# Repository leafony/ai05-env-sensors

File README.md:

# AI05 Env Sensors

温湿度・気圧・3軸加速度を測定する Leafony リーフの KiCad プロジェクトです。

## 構成部品

| 部品 | メーカー | 機能 |
| --- | --- | --- |
| SHT40-AD1B-R2 | Sensirion | 温湿度（選択実装） |
| SGP40-D-R4 | Sensirion | VOC ガス（選択実装） |
| BME280 / BME680 | Bosch Sensortec | 温湿度・気圧 / 温湿度・気圧・ガス（選択実装） |
| LIS2DW12TR | STMicroelectronics | 3軸加速度 |
| SM04B-SRSS-TB | JST | Qwiic、4極、1 mm ピッチ、横出し |

全センサーは Leafony Bus の **3.3 V・I²C** に接続します。基板は **23 × 20 mm、4層、板厚 0.8 mm** です。

SHT40とSGP40は現行の回路図・BOMではDNPです。標準構成ではBME280とLIS2DW12を実装します。

BME280 と BME680 は専用フットプリントをそれぞれ設け、**片方だけを実装**します。標準構成は BME280（U3、C5、C6）を実装し、BME680（U4、C7、C8）を DNP とします。BME680 構成ではこの実装・未実装を入れ替えます。

| センサー | I²C アドレス |
| --- | --- |
| SHT40 | `0x44` |
| SGP40 | `0x59` |
| BME280 / BME680 | `0x76` |
| LIS2DW12 | `0x18`（SDO/SA0をGNDに接続） |

LIS2DW12 の割り込み端子はD3に接続されます。I2C通信速度の上限は 400 kHz です。

SDA/SCL のプルアップはAP03 STM32リーフに搭載されているためDNPとします。既存 AI01 4-Sensors とは加速度センサーの割り込みピンD3が重複するため、同じバスに同時接続しないでください。

## サンプルコード

[`platformio/`](platformio/README.md) にサンプルをフォルダごとの独立したPlatformIOプロジェクトとして配置しています。[`read_sensors`](platformio/read_sensors/README.md) はAP03 STM32向けに、起動時にセンサーを検出・初期化し、1秒ごとに測定値をシリアル（115200 bps）へ出力します。未実装センサーはスキップします。

[`accel_wakeup`](platformio/accel_wakeup/README.md) はLIS2DW12の動き検出をD3の割り込みで受け取り、検出時刻・回数・軸・加速度をシリアル出力します。

[`accel_shock_fifo`](platformio/accel_shock_fifo/README.md) は衝撃検出後の加速度100点をFIFOから取得します。付属のブラウザービューアで3軸の波形表示とCSV保存ができます。

## ライセンス

MIT

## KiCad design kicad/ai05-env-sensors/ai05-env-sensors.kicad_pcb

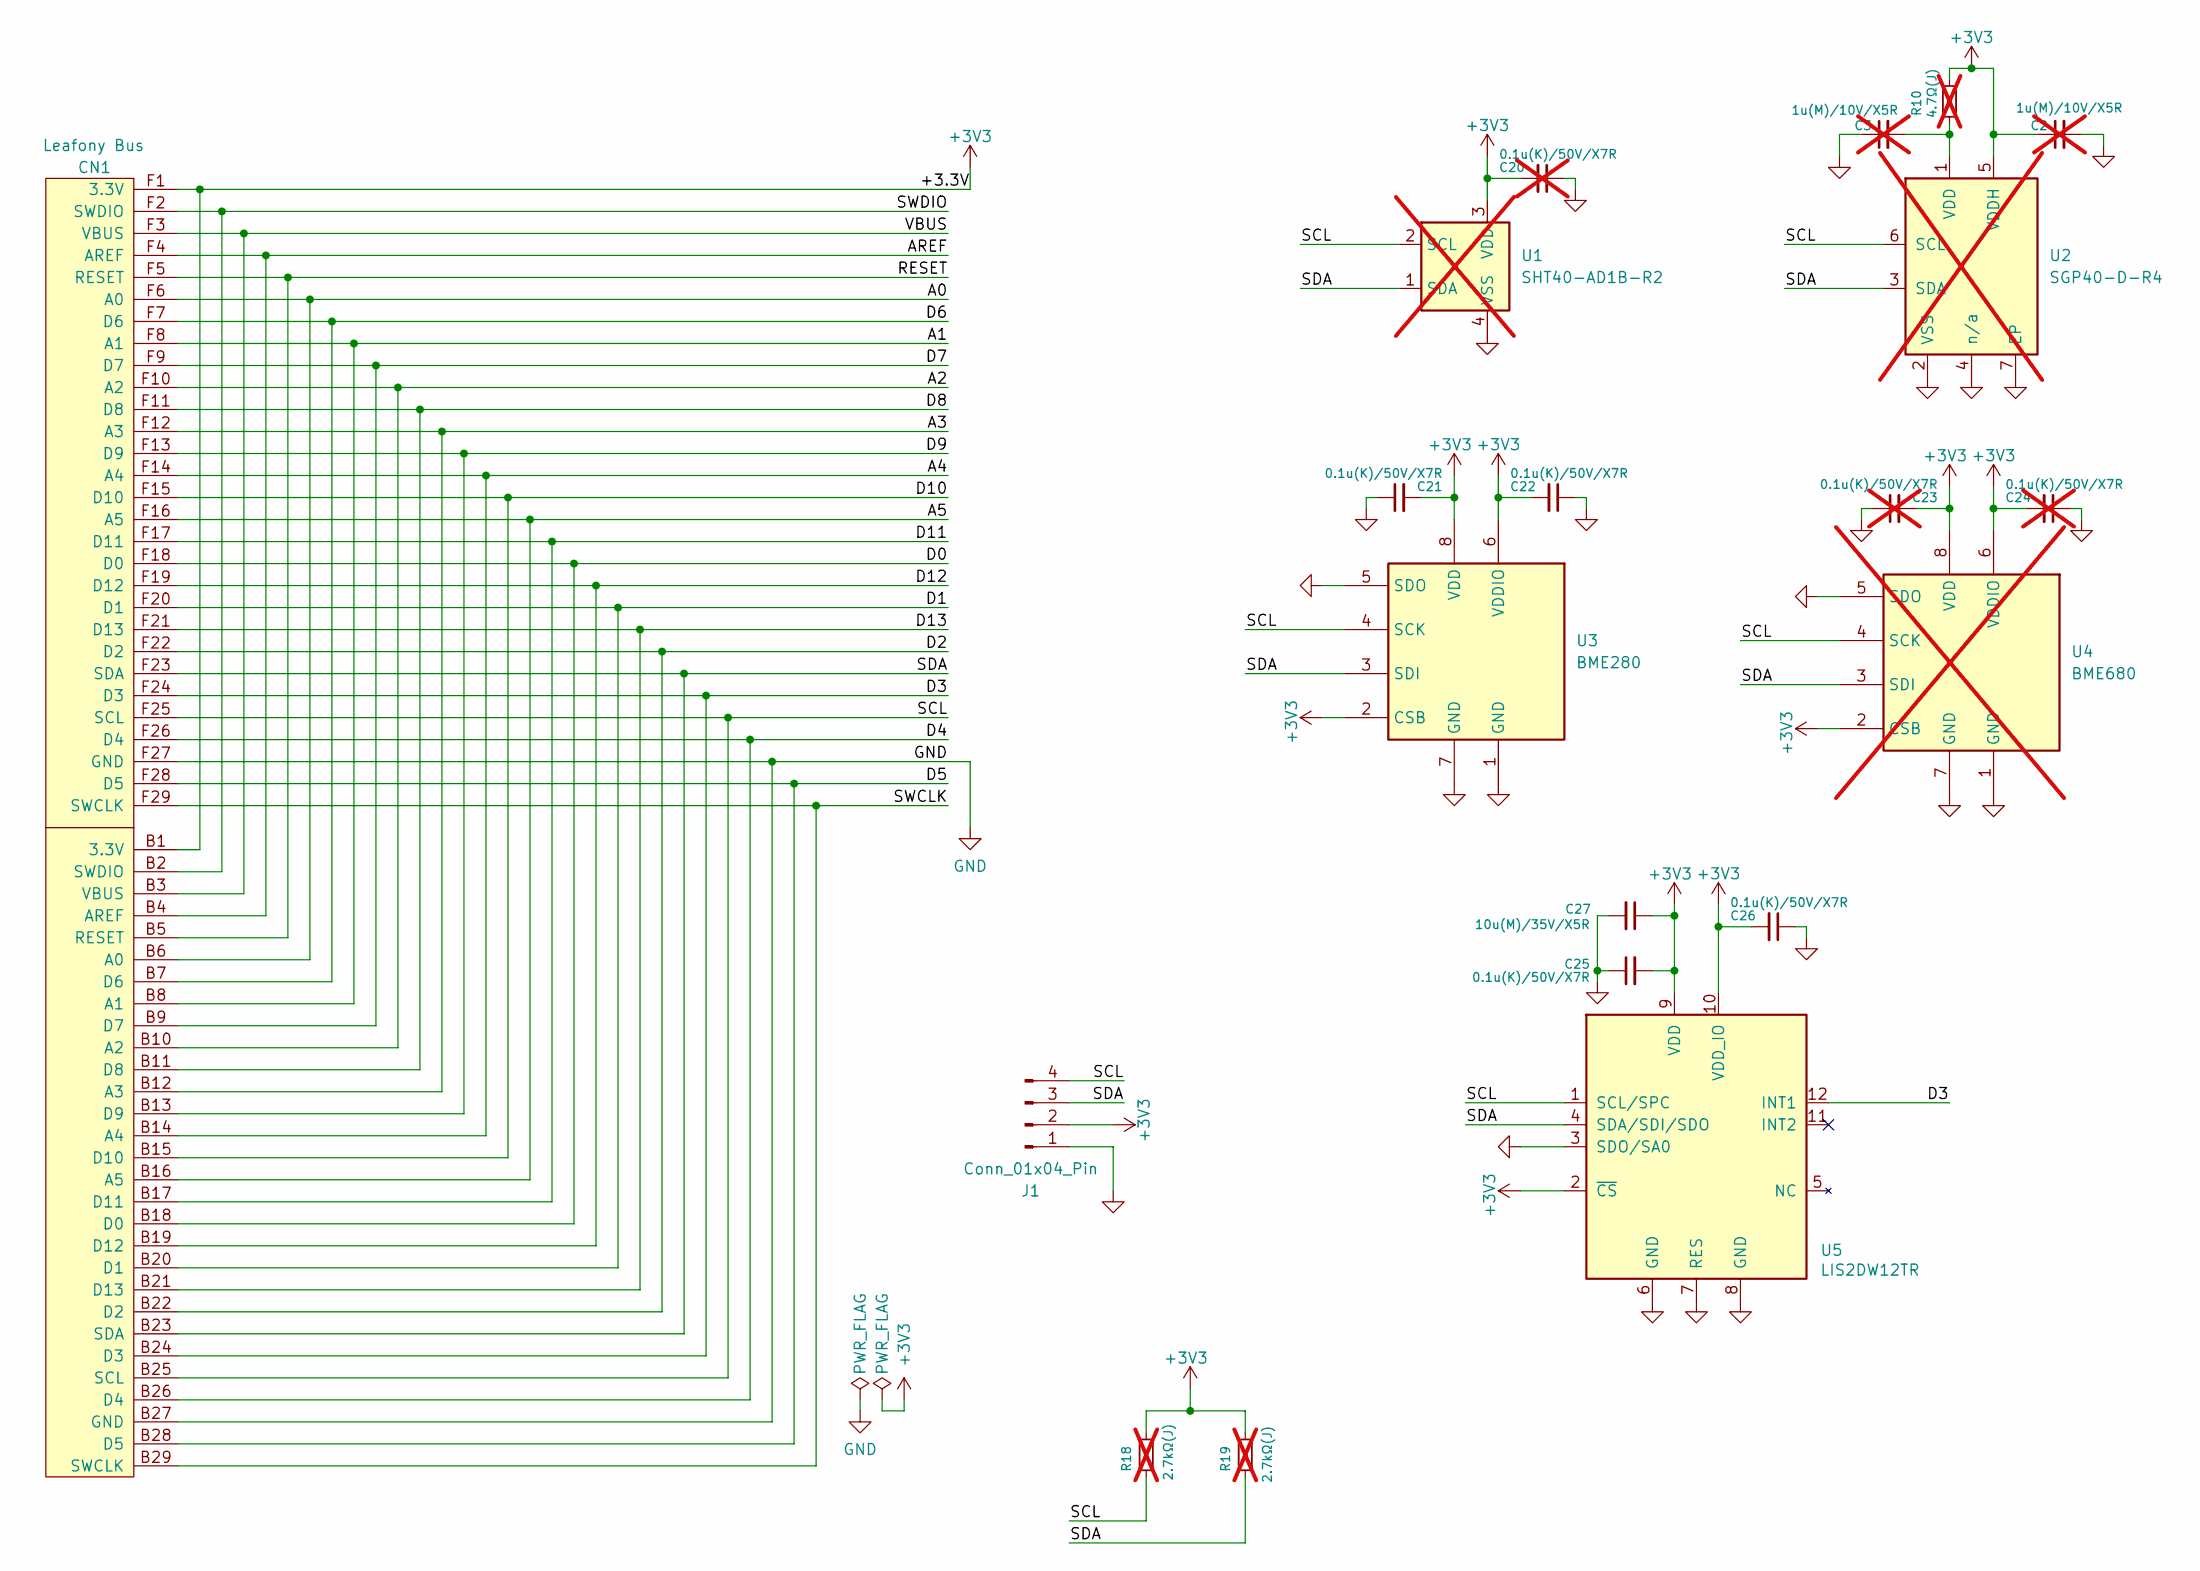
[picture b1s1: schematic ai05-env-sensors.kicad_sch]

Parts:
C2, C3: 1u(M)/10V/X5R; C_0402_1005Metric; MPN CC0402MRX5R6BB105; Digi-Key Product Number 311-1732-1-ND; not fitted
C20, C23, C24: 0.1u(K)/50V/X7R; C_0402_1005Metric; MPN CC0402KRX7R9BB104; not fitted
C21, C22, C25, C26: 0.1u(K)/50V/X7R; C_0402_1005Metric; MPN CC0402KRX7R9BB104
C27: 10u(M)/35V/X5R; C_0603_1608Metric; MPN GRM188R6YA106MA73J; Digi-Key Product Number 490-GRM188R6YA106MA73JCT-ND
CN1: Leafony Bus; CN_F29_B29
J1: Conn_01x04_Pin; PinHeader_1x04_P2.54mm_Horizontal
R10: 4.7Ω(J); R_0402_1005Metric; MPN RC0402JR-074R7L; Digi-Key Product Number 311-4.7JRCT-ND; not fitted
R18, R19: 2.7kΩ(J); R_0402_1005Metric; MPN RC0402JR-072K7L; Digi-Key Product Number 311-2.7KJRCT-ND; not fitted
U1: SHT40-AD1B-R2; Sensirion_DFN-4_1.5x1.5mm_P0.8mm_SHT4x_NoCentralPad; MPN SHT40-AD1B-R2; not fitted
U2: SGP40-D-R4; Sensirion_DFN-6-1EP_2.44x2.44mm_P0.8mm_SGP40; MPN SGP40-D-R4; not fitted
U3: BME280; Bosch_LGA-8_2.5x2.5mm_P0.65mm_ClockwisePinNumbering; MPN BME280
U4: BME680; Bosch_LGA-8_3x3mm_P0.8mm_ClockwisePinNumbering_Recommended; MPN BME680; not fitted
U5: LIS2DW12TR; LGA-12_2x2mm_P0.5mm; MPN LIS2DW12TR

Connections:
+3V3: C2.1, C20.2, C21.2, C22.2, C23.2, C24.2, C25.2, C26.2, C27.1, CN1.B1 (3.3V), CN1.F1 (3.3V), J1.2, R10.2, R18.1, R19.1, U1.3 (VDD), U2.5 (VDDH), U3.2 (CSB), U3.6 (VDDIO), U3.8 (VDD), U4.2 (CSB), U4.6 (VDDIO), U4.8 (VDD), U5.2 (~CS), U5.9 (VDD), U5.10 (VDD_IO)
/A0: CN1.B6 (A0), CN1.F6 (A0)
/A1: CN1.B8 (A1), CN1.F8 (A1)
/A2: CN1.B10 (A2), CN1.F10 (A2)
/A3: CN1.B12 (A3), CN1.F12 (A3)
/A4: CN1.B14 (A4), CN1.F14 (A4)
/A5: CN1.B16 (A5), CN1.F16 (A5)
/AREF: CN1.B4 (AREF), CN1.F4 (AREF)
/D0: CN1.B18 (D0), CN1.F18 (D0)
/D1: CN1.B20 (D1), CN1.F20 (D1)
/D2: CN1.B22 (D2), CN1.F22 (D2)
/D3: CN1.B24 (D3), CN1.F24 (D3), U5.12 (INT1)
/D4: CN1.B26 (D4), CN1.F26 (D4)
/D5: CN1.B28 (D5), CN1.F28 (D5)
/D6: CN1.B7 (D6), CN1.F7 (D6)
/D7: CN1.B9 (D7), CN1.F9 (D7)
/D8: CN1.B11 (D8), CN1.F11 (D8)
/D9: CN1.B13 (D9), CN1.F13 (D9)
/D10: CN1.B15 (D10), CN1.F15 (D10)
/D11: CN1.B17 (D11), CN1.F17 (D11)
/D12: CN1.B19 (D12), CN1.F19 (D12)
/D13: CN1.B21 (D13), CN1.F21 (D13)
/RESET: CN1.B5 (RESET), CN1.F5 (RESET)
/SCL: CN1.B25 (SCL), CN1.F25 (SCL), J1.4, R18.2, U1.2 (SCL), U2.6 (SCL), U3.4 (SCK), U4.4 (SCK), U5.1 (SCL/SPC)
/SDA: CN1.B23 (SDA), CN1.F23 (SDA), J1.3, R19.2, U1.1 (SDA), U2.3 (SDA), U3.3 (SDI), U4.3 (SDI), U5.4 (SDA/SDI/SDO)
/SWCLK: CN1.B29 (SWCLK), CN1.F29 (SWCLK)
/SWDIO: CN1.B2 (SWDIO), CN1.F2 (SWDIO)
/VBUS: CN1.B3 (VBUS), CN1.F3 (VBUS)
GND: C2.2, C3.1, C20.1, C21.1, C22.1, C23.1, C24.1, C25.1, C26.1, C27.2, CN1.B27 (GND), CN1.F27 (GND), J1.1, U1.4 (VSS), U2.2 (VSS), U2.4 (n/a), U2.7 (EP), U3.1 (GND), U3.5 (SDO), U3.7 (GND), U4.1 (GND), U4.5 (SDO), U4.7 (GND), U5.3 (SDO/SA0), U5.6 (GND), U5.7 (RES), U5.8 (GND)
unnamed: C3.2, R10.1, U2.1 (VDD)

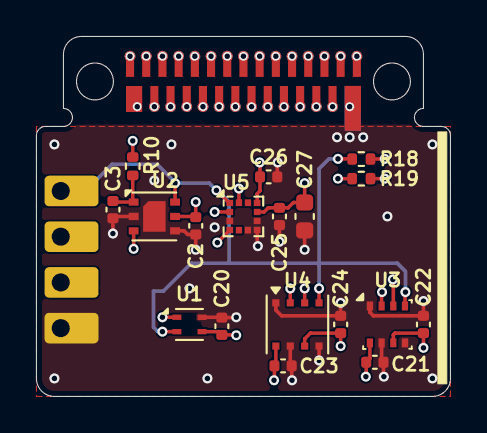
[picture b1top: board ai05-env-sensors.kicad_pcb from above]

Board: 4 copper layers, 23.0 x 20.0 mm, 20 parts (0 on the bottom side), 30 nets.
